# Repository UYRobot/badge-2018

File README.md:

# Badge UYRobot 2018
Badge for teaching how to solder electronic components.

We designed this badge to teach kids how to use the soldering iron and some basics about circuits.

**Feel free to make your own, remix or hack it!
Please show us your work @UYRobot on [Instagram](www.instagram.com/uyrobot) or [Facebook](www.facebook.com/uyrobot).**

Designed with :heart: in Uruguay.

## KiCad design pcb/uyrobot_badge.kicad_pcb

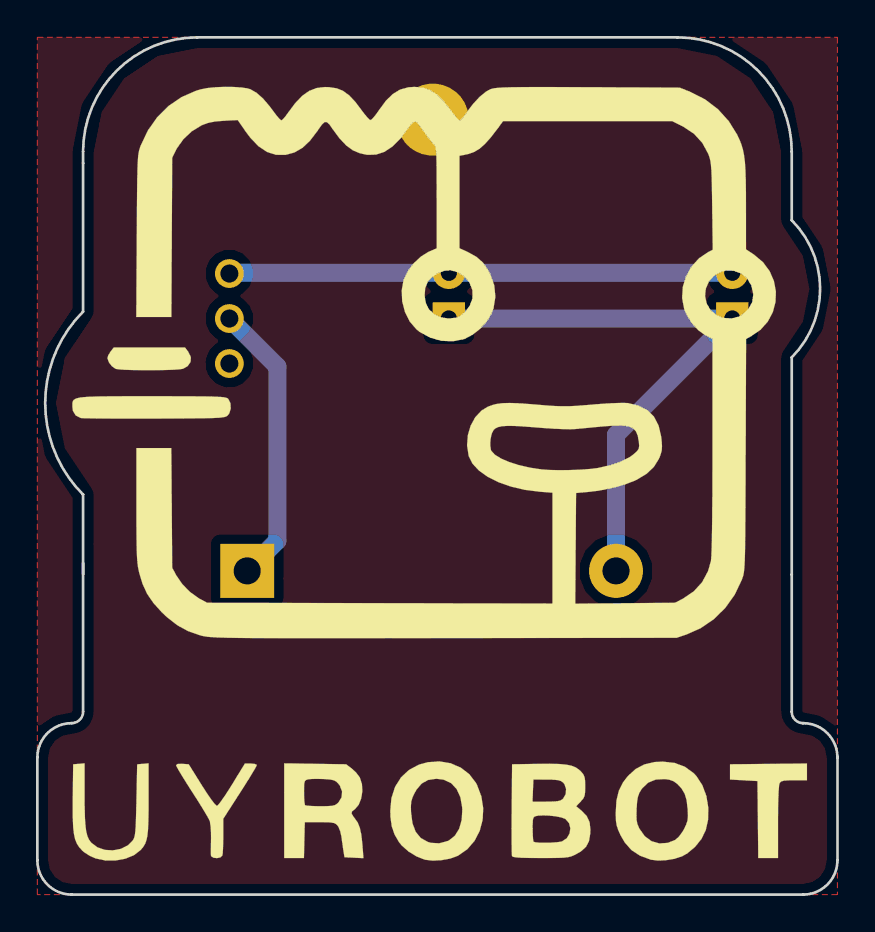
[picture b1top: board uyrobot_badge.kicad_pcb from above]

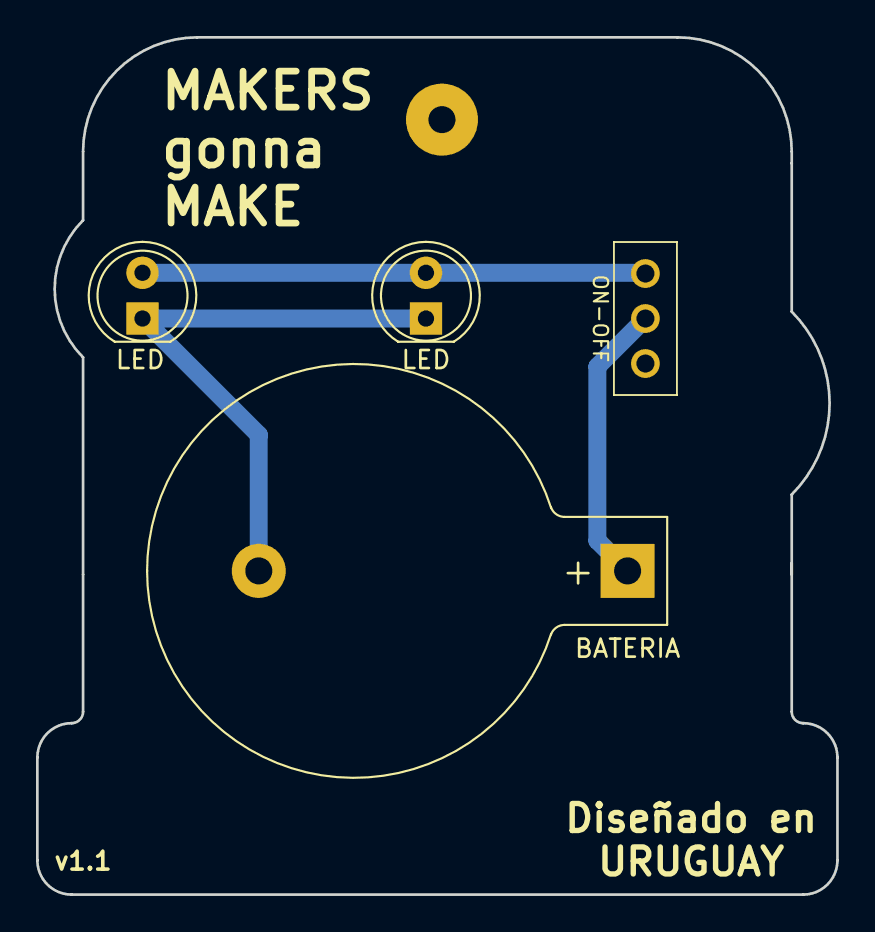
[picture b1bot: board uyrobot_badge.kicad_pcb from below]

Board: 2 copper layers, 44.4 x 47.6 mm, 4 parts (4 on the bottom side), 3 nets.

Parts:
BATERIA: Battery_Cell; BatteryHolder_Keystone_103_1x20mm
LED: LED; LED_D5.0mm
LED#2: LED; LED_D5.0mm
ON-OFF: SW_DIP_x01; SS12D00

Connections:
unnamed: BATERIA.1, ON-OFF.2
unnamed: BATERIA.2, LED.1, LED#2.1
unnamed: LED.2, LED#2.2, ON-OFF.1

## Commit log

2018-10-10 Initial commit. PCB files added. uyrobot_badge.zip contains gerber files ready.
